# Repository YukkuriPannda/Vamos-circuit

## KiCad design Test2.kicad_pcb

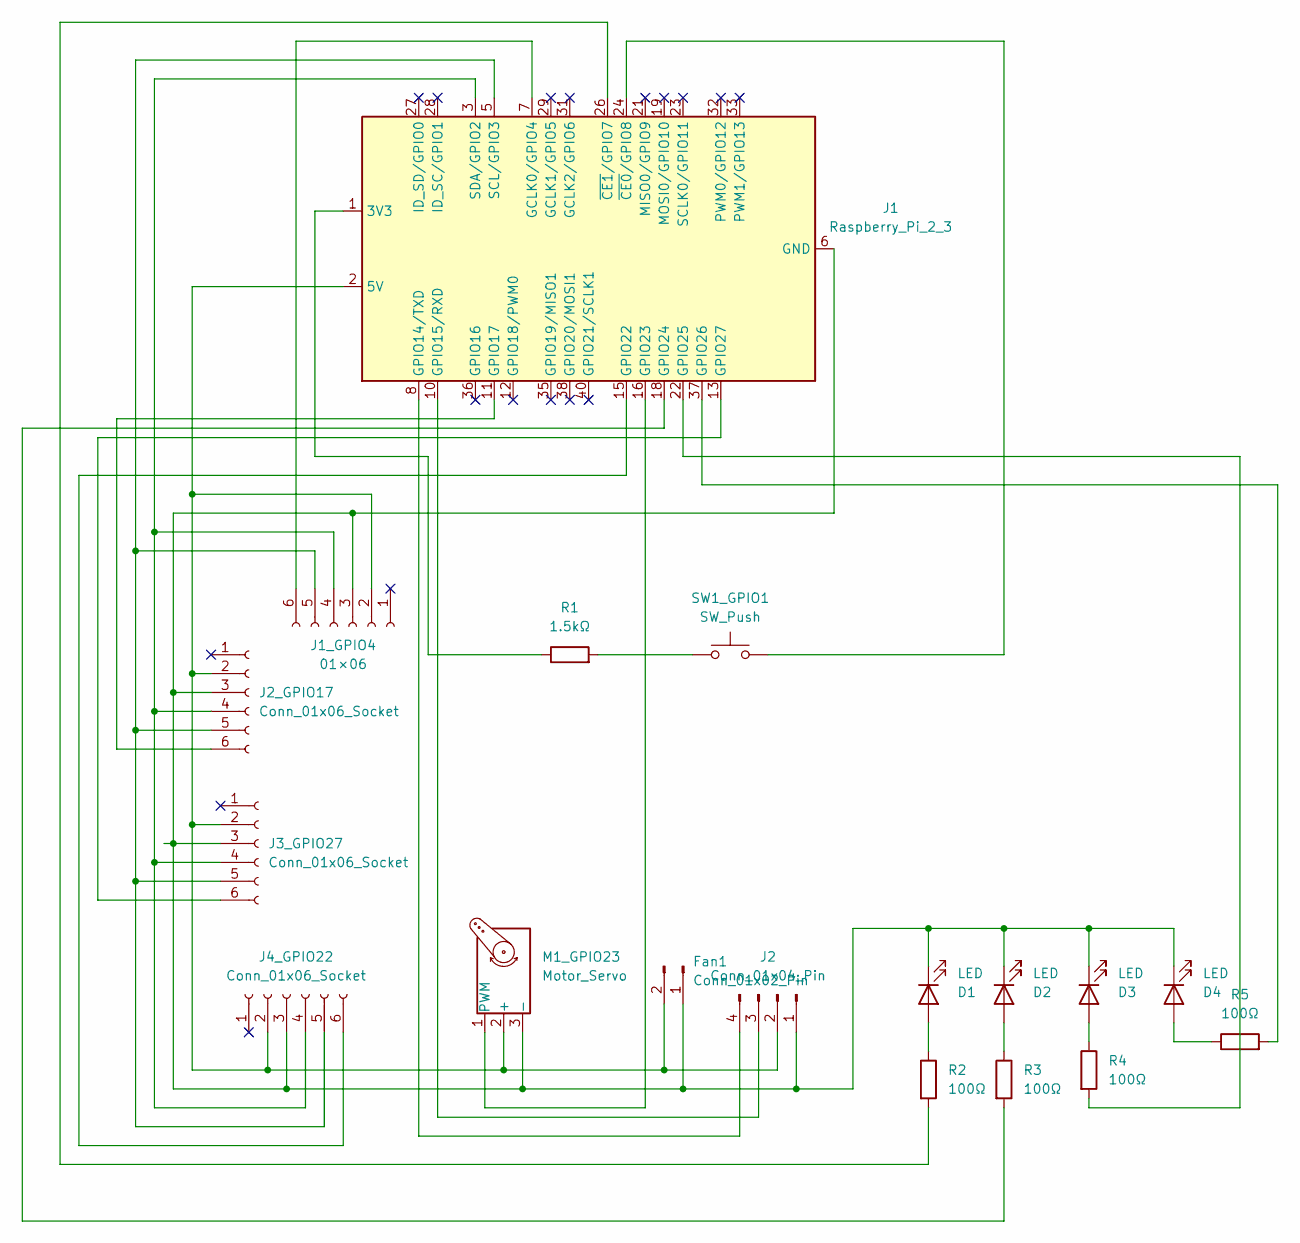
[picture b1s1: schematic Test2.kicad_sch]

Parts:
D1, D2, D3, D4: LED
Fan1: Conn_01x02_Pin; PinHeader_1x02_P2.54mm_Vertical
J1: Raspberry_Pi_2_3; PinSocket_2x20_P2.54mm_Vertical
J1_GPIO4: 01×06; Connector_JST.prettyJST_ZH_B6B-ZR_1x06_P1.50mm_Vertical
J2: Conn_01x04_Pin; Grove_1x04
J2_GPIO17, J3_GPIO27, J4_GPIO22: Conn_01x06_Socket; Connector_JST.prettyJST_ZH_B6B-ZR_1x06_P1.50mm_Vertical
M1_GPIO23: Motor_Servo; PinHeader_1x03_P2.54mm_Vertical
R1: 1.5kΩ; R_0805_2012Metric
R2, R3, R4, R5: 100Ω; R_0805_2012Metric
SW1_GPIO1: SW_Push; PushButton

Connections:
unnamed: D1.2 (A), R2.1
unnamed: D2.2 (A), R3.1
unnamed: D3.2 (A), R4.1
unnamed: D4.2 (A), R5.1
unnamed: Fan1.2, J1.2 (5V), J1.4 (5V), J1_GPIO4.2, J2.2, J2_GPIO17.2, J3_GPIO27.2, J4_GPIO22.2, M1_GPIO23.2 (+)
unnamed 5: J1.1 (3V3), J1.17 (3V3), R1.1; also elsewhere on the board
unnamed: J1.7 (GCLK0/GPIO4), J1_GPIO4.6
unnamed: J1.8 (GPIO14/TXD), J2.4
unnamed: J1.10 (GPIO15/RXD), J2.3
unnamed: J1.11 (GPIO17), J2_GPIO17.6
unnamed: J1.15 (GPIO22), J4_GPIO22.6
unnamed: J1.16 (GPIO23), M1_GPIO23.1 (PWM)
unnamed: J1.18 (GPIO24), R3.2
unnamed: J1.22 (GPIO25), R4.2
unnamed: J1.37 (GPIO26), R5.2
unnamed: J1.13 (GPIO27), J3_GPIO27.6
unnamed: J1.5 (SCL/GPIO3), J1_GPIO4.5, J2_GPIO17.5, J3_GPIO27.5, J4_GPIO22.5
unnamed: J1.3 (SDA/GPIO2), J1_GPIO4.4, J2_GPIO17.4, J3_GPIO27.4, J4_GPIO22.4
unnamed: J1.24 (~CE0/GPIO8), SW1_GPIO1.3
unnamed: J1.26 (~CE1/GPIO7), R2.2
unnamed: R1.2, SW1_GPIO1.1

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
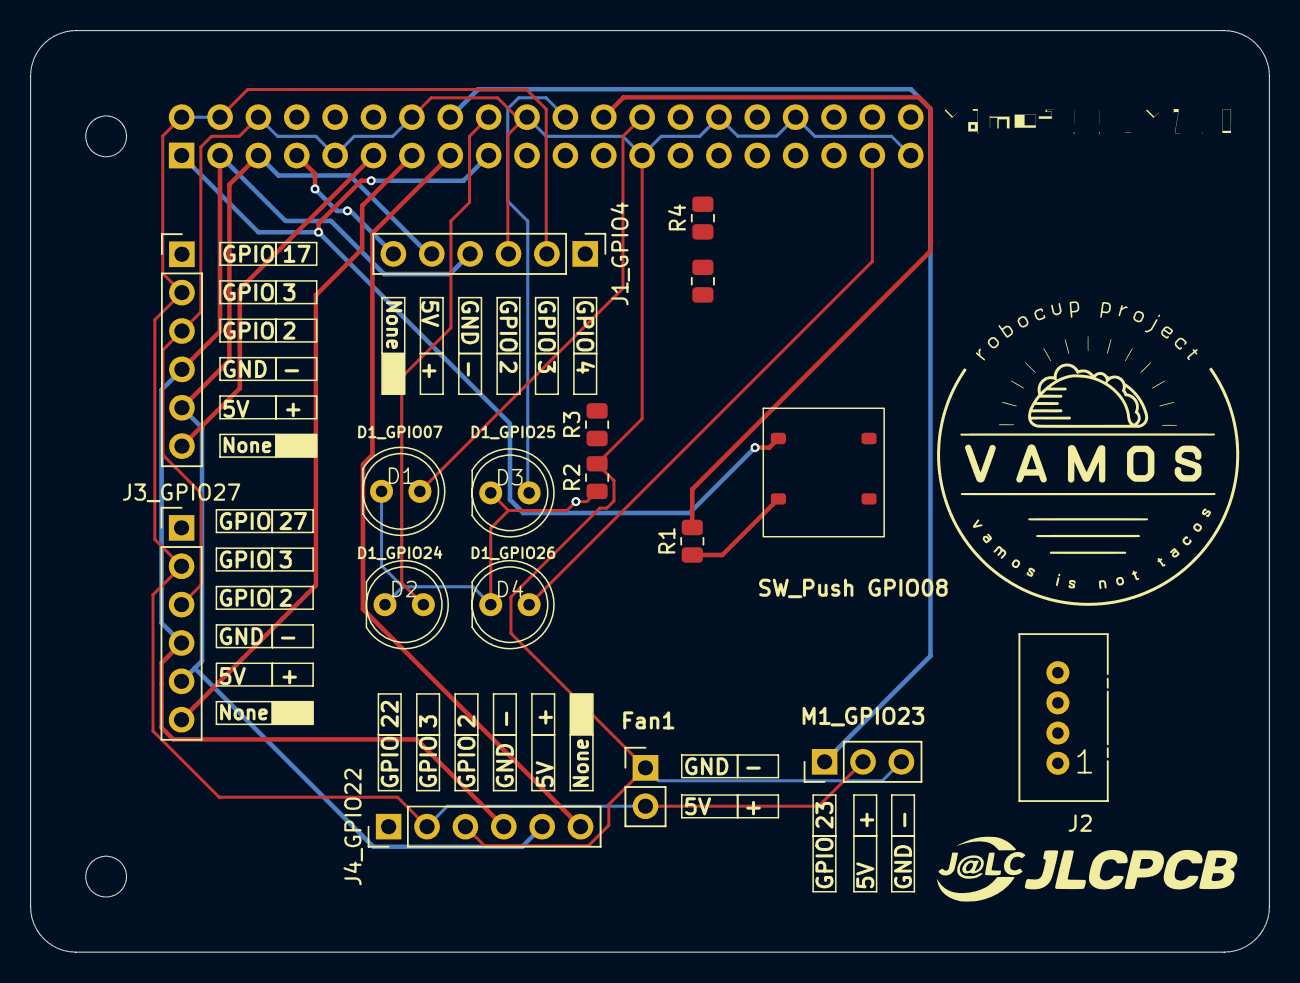
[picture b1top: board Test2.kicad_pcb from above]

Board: 2 copper layers, 82.0 x 61.0 mm, 21 parts (1 on the bottom side), 21 nets.

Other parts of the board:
REF1: MountingHole_2.7mm_M2.5
SW1_GPIO8: SW_Push; PushButton
jlcpcb: LOGO; jlcpcb
vamos: LOGO; vamoslogo

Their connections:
unnamed 5: SW1_GPIO8.1; also elsewhere on the board

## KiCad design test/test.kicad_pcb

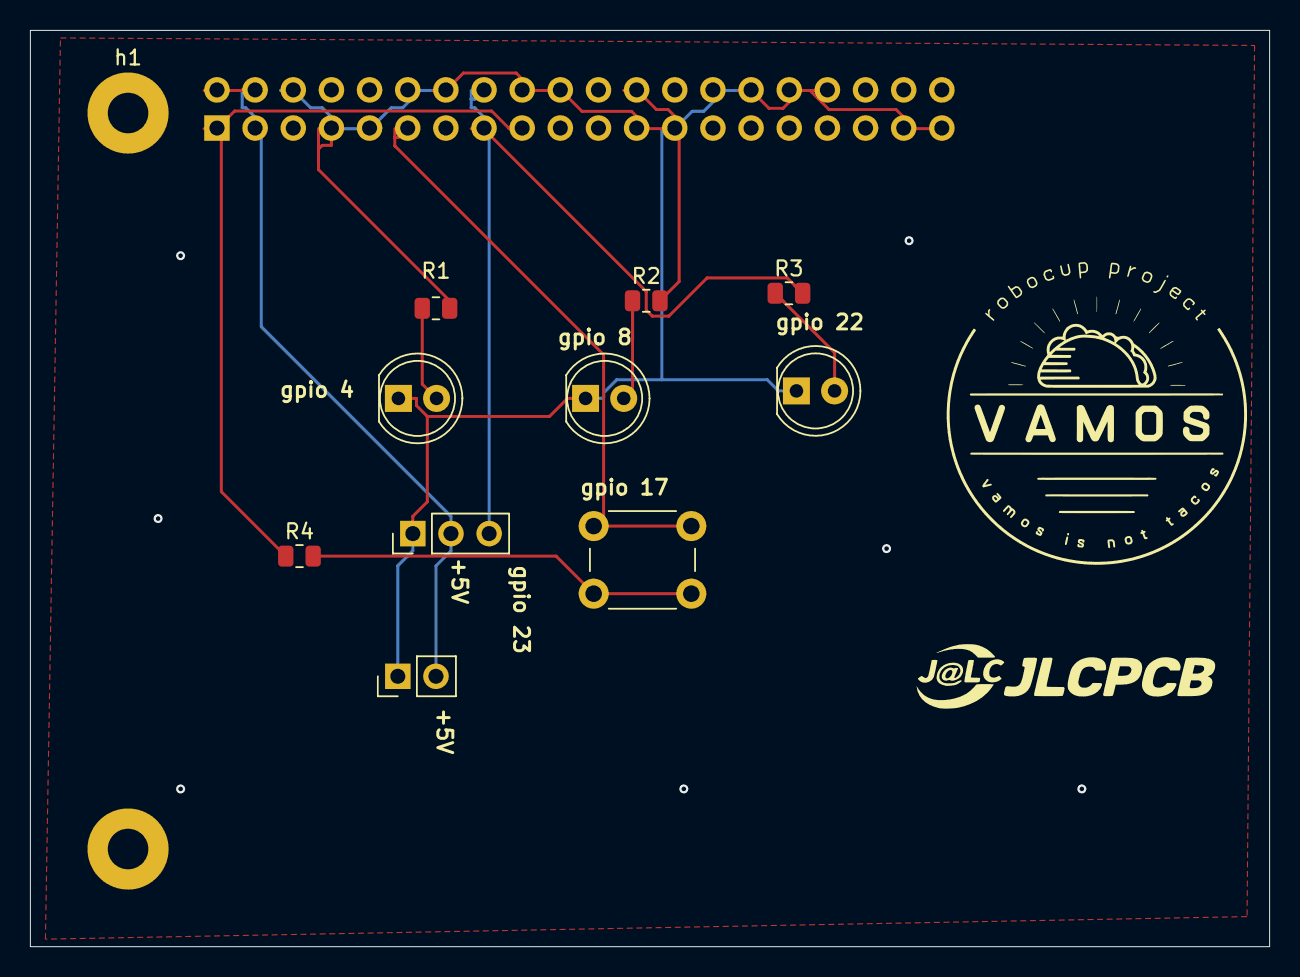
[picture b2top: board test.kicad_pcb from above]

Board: 2 copper layers, 82.5 x 61.0 mm, 15 parts (1 on the bottom side), 12 nets.

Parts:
D1, D2, D3: LED; LED_D5.0mm
J1: Conn_01x02_Pin; PinHeader_1x02_P2.54mm_Vertical
J2: Raspberry_Pi_2_3; PinSocket_2x20_P2.54mm_Vertical
J3: Conn_01x03_Pin; PinHeader_1x03_P2.54mm_Vertical
R1, R2: 200R; R_0805_2012Metric
R3: 200; R_0805_2012Metric
R4: 1K; R_0805_2012Metric
SW1: SW_Push; SW_PUSH_6mm_H9.5mm
h1, h2: MountingHole_2.7mm_M2.5_Pad
jlcpcb: LOGO; jlcpcb
vamos: LOGO; vamoslogo

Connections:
unnamed: D1.2 (A), R1.1
unnamed: D1.1 (K), D2.1 (K), D3.1 (K), J1.1, J2.6 (GND), J2.9 (GND), J2.14 (GND), J2.20 (GND), J2.25 (GND), J2.30 (GND), J2.34 (GND), J2.39 (GND), J3.1
unnamed: D2.2 (A), R2.1
unnamed: D3.2 (A), R3.1
unnamed: J1.2, J2.2 (5V), J2.4 (5V), J3.2
unnamed: J2.1 (3V3), J2.17 (3V3), R4.1
unnamed: J2.7 (GCLK0/GPIO4), R1.2
unnamed: J2.11 (GPIO17), SW1.2
unnamed: J2.15 (GPIO22), R3.2
unnamed: J2.16 (GPIO23), J3.3
unnamed: J2.24 (~CE0/GPIO8), R2.2
unnamed: R4.2, SW1.1

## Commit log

2024-10-22 Vamos-circuit
